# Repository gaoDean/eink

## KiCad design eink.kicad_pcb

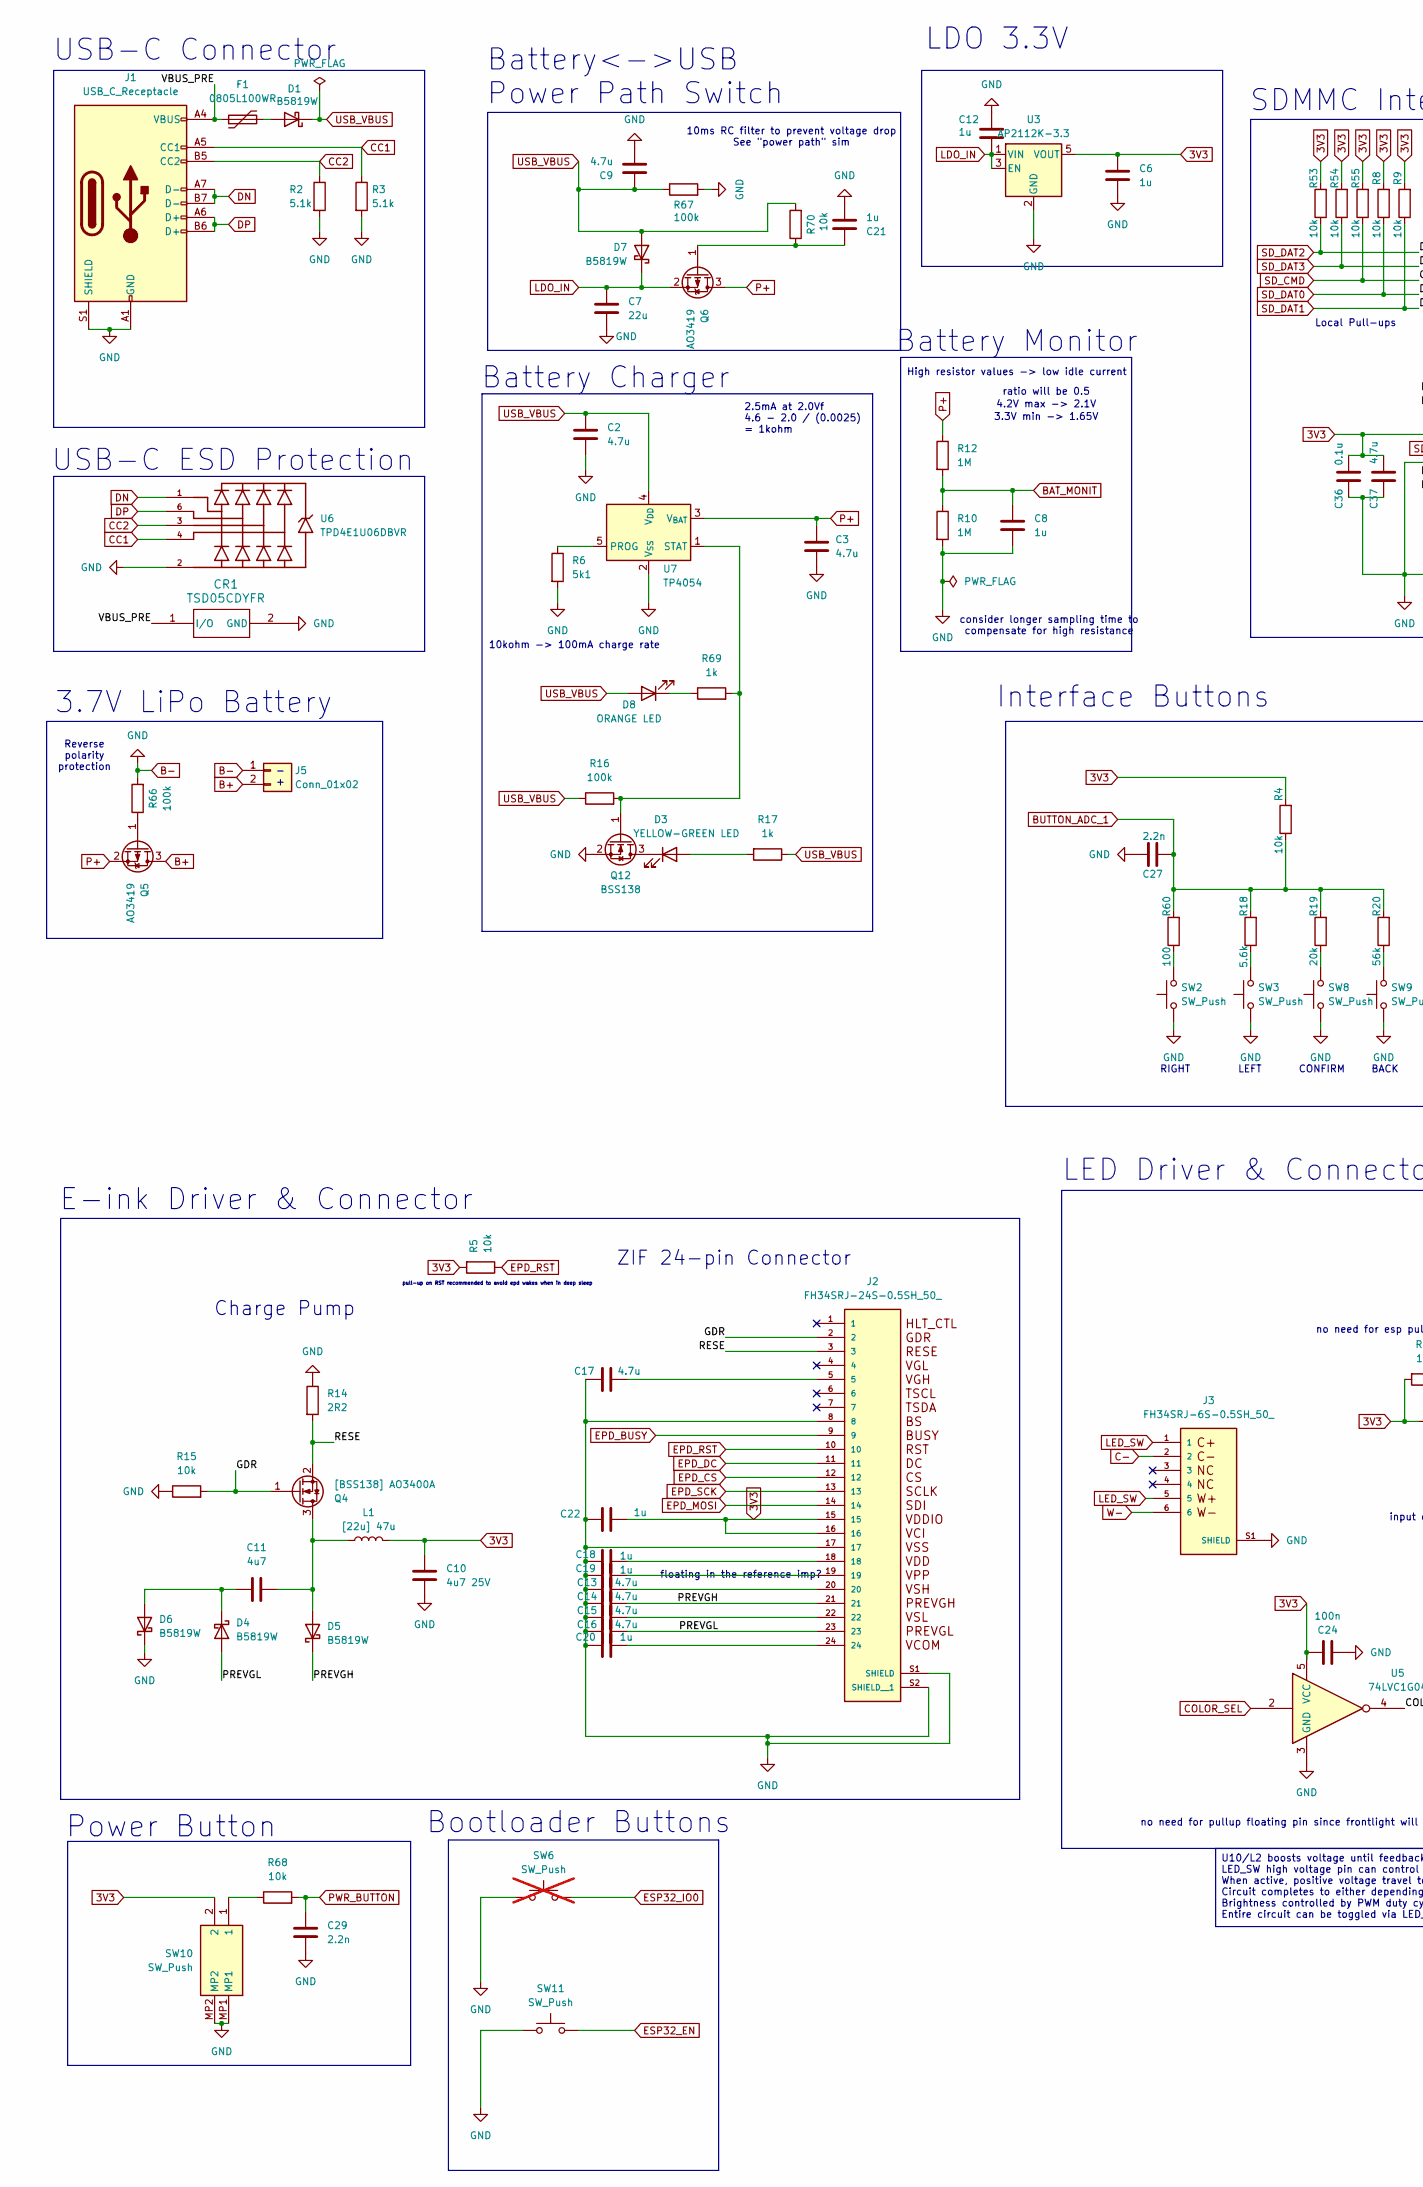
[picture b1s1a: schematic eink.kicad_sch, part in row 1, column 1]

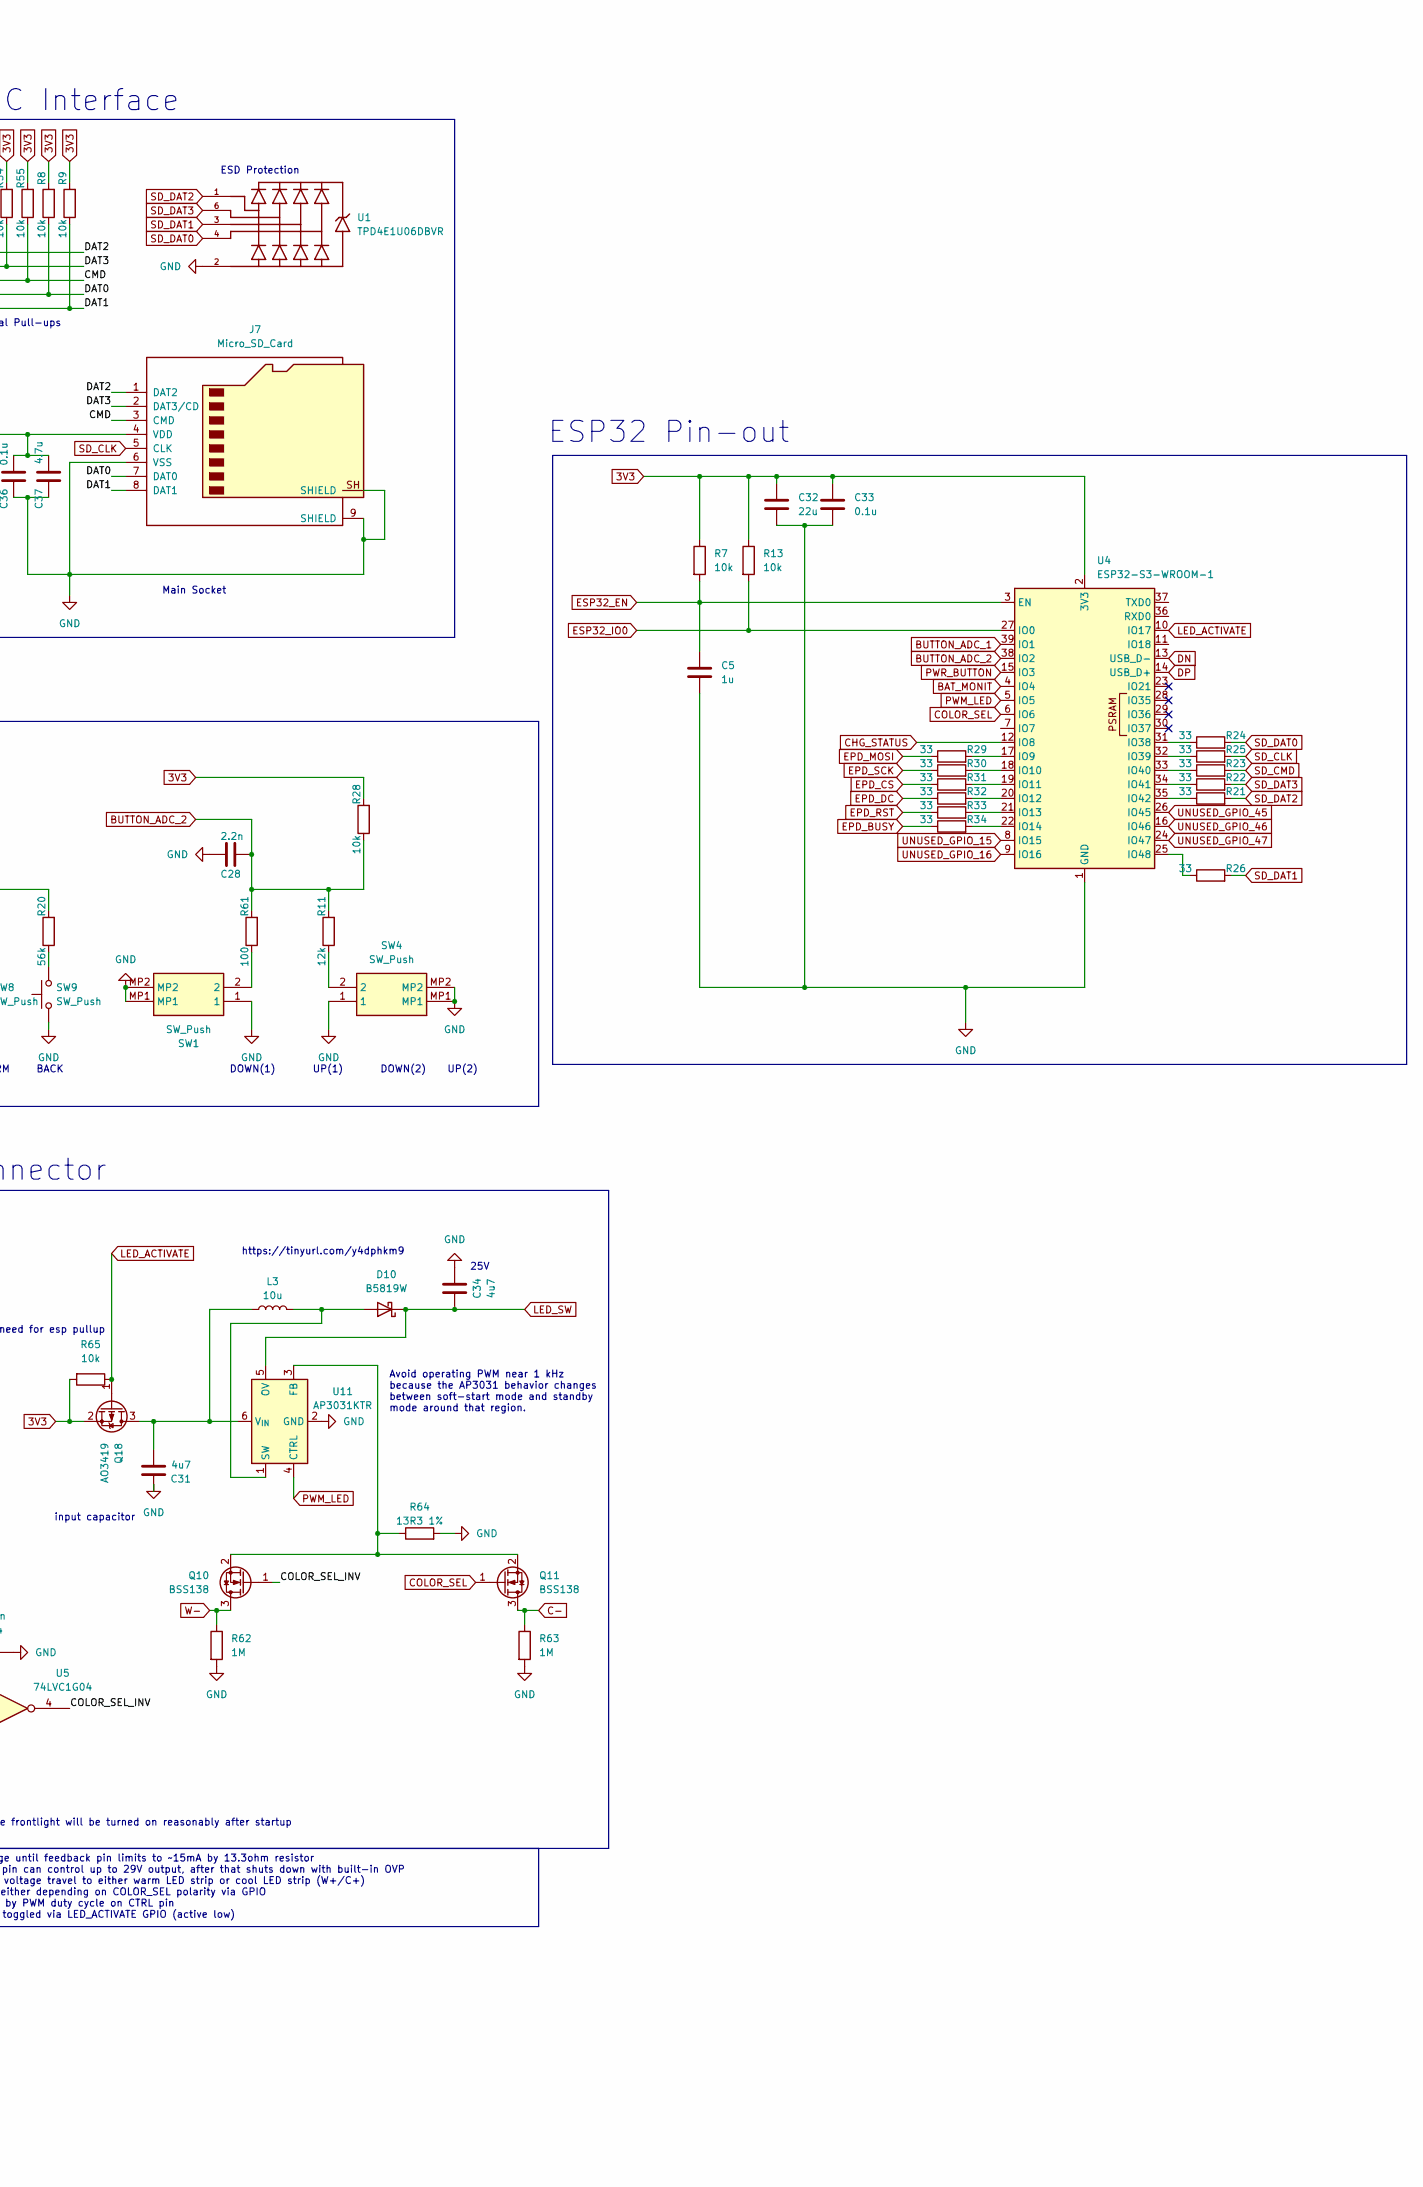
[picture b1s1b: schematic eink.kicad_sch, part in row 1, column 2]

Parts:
C2, C3, C9, C13, C14, C15, C16, C17, C37: 4.7u; C_0805_2012Metric_Pad1.18x1.45mm_HandSolder
C5, C6, C8, C12, C18, C19, C20, C21, C22: 1u; C_0805_2012Metric_Pad1.18x1.45mm_HandSolder
C7, C32: 22u; C_0805_2012Metric_Pad1.18x1.45mm_HandSolder
C10: 4u7 25V; C_0805_2012Metric_Pad1.18x1.45mm_HandSolder
C11, C31, C34: 4u7; C_0805_2012Metric_Pad1.18x1.45mm_HandSolder
C24: 100n; C_0805_2012Metric_Pad1.18x1.45mm_HandSolder
C27, C28, C29: 2.2n; C_0805_2012Metric_Pad1.18x1.45mm_HandSolder
C33, C36: 0.1u; C_0805_2012Metric_Pad1.18x1.45mm_HandSolder
CR1: TSD05CDYFR; D_SOD-323_HandSoldering
D1, D4, D5, D6, D7, D10: B5819W; D_SOD-123
D3: YELLOW-GREEN LED; LED_0805_2012Metric_Pad1.15x1.40mm_HandSolder
D8: ORANGE LED; LED_0805_2012Metric_Pad1.15x1.40mm_HandSolder
F1: 0805L100WR; Fuse_0805_2012Metric_Pad1.15x1.40mm_HandSolder
J1: USB_C_Receptacle; USB_C_Receptacle_TYPE-C-16P-CB1-6-073
J2: FH34SRJ-24S-0.5SH_50_; HRS_FH34SRJ-24S-0.5SH_50_
J3: FH34SRJ-6S-0.5SH_50_; HRS_FH34SRJ-6S-0.5SH_50_; DigiKey_Part_Number H125773CT-ND
J5: Conn_01x02; Battery pads
J7: Micro_SD_Card; microSD_HC_Hirose_DM3AT-SF-PEJM5
L1: [22u] 47u; IND_SRN3010C-100M
L3: 10u; IND_SRN3010C-100M
Q4: [BSS138] AO3400A; SOT-23
Q5, Q6, Q18: AO3419; SOT-23_Handsoldering
Q10, Q11, Q12: BSS138; SOT-23
R2, R3: 5.1k; R_0805_2012Metric_Pad1.20x1.40mm_HandSolder
R4, R5, R7, R8, R9, R13, R15, R28, R53, R54, R55, R65, R68, R70: 10k; R_0805_2012Metric_Pad1.20x1.40mm_HandSolder
R6: 5k1; R_0805_2012Metric_Pad1.20x1.40mm_HandSolder
R10, R12, R62, R63: 1M; R_0805_2012Metric_Pad1.20x1.40mm_HandSolder
R11: 12k; R_0805_2012Metric_Pad1.20x1.40mm_HandSolder
R14: 2R2; R_0805_2012Metric_Pad1.20x1.40mm_HandSolder
R16, R66, R67: 100k; R_0805_2012Metric_Pad1.20x1.40mm_HandSolder
R17, R69: 1k; R_0805_2012Metric_Pad1.20x1.40mm_HandSolder
R18: 5.6k; R_0805_2012Metric_Pad1.20x1.40mm_HandSolder
R19: 20k; R_0805_2012Metric_Pad1.20x1.40mm_HandSolder
R20: 56k; R_0805_2012Metric_Pad1.20x1.40mm_HandSolder
R21, R22, R23, R24, R25, R26, R29, R30, R31, R32, R33, R34: 33; R_0805_2012Metric_Pad1.20x1.40mm_HandSolder
R60, R61: 100; R_0805_2012Metric_Pad1.20x1.40mm_HandSolder
R64: 13R3 1%; R_0805_2012Metric_Pad1.20x1.40mm_HandSolder
SW1, SW4, SW10: SW_Push; SKSNLAE010; Mouser Part Number 688-SKSNLAE010
SW2, SW3, SW8, SW9: SW_Push; SKQGABE010_ALPS_Reverse
SW6: SW_Push; TestPoint_Bridge_Pitch2.54mm_Drill1.0mm; not fitted
SW11: SW_Push; TestPoint_Bridge_Pitch2.54mm_Drill1.0mm
U1, U6: TPD4E1U06DBVR; SOT-23-6_Handsoldering; PARTREV D; DigiKey_Part_Number 296-35965-1-ND
U3: AP2112K-3.3; SOT-23-5_HandSoldering
U4: ESP32-S3-WROOM-1
U5: 74LVC1G04; SOT-23-5_HandSoldering
U7: TP4054; SOT-23-5
U11: AP3031KTR; SOT-23-6_Handsoldering

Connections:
3V3: C6.1, C10.2, C22.2, C24.1, C32.1, C33.1, C36.2, C37.2, J2.15, J2.16, J7.4 (VDD), L1.2, Q18.2 (S), R4.2, R5.2, R7.1, R8.2, R9.2, R13.1, R28.2, R53.2, R54.2, R55.2, R65.2, SW10.2, U3.5 (VOUT), U4.2 (3V3), U5.5 (VCC)
/COLOR_SEL_INV: Q10.1 (G), U5.4
/GDR: J2.2, Q4.1 (G), R15.2
/PREVGH: C14.2, D5.1 (K), J2.21
/PREVGL: C16.2, D4.2 (A), J2.23
/RESE: J2.3, Q4.2 (S), R14.2
/VBUS_PRE: CR1.1 (I/O), F1.1, J1.A4 (VBUS), J1.A9 (VBUS), J1.B4 (VBUS), J1.B9 (VBUS)
B+: J5.2, Q5.3 (D)
B-: C2.2, C3.2, C5.2, C6.2, C7.2, C8.2, C9.2, C10.1, C12.2, C13.1, C14.1, C15.1, C16.1, C17.1, C18.1, C19.1, C20.1, C21.2, C22.1, C24.2, C27.1, C28.1, C29.2, C31.1, C32.2, C33.2, C34.1, C36.1, C37.1, CR1.2 (GND), D6.1 (K), J1.A1 (GND), J1.A12 (GND), J1.B1 (GND), J1.B12 (GND), J1.S1 (SHIELD), J2.8, J2.17, J2.S1 (SHIELD), J2.S2 (SHIELD__1), J3.S1 (SHIELD), J3.S2 (SHIELD), J5.1, J7.6 (VSS), J7.9 (SHIELD), J7.SH (SHIELD), Q12.2 (S), R2.2, R3.2, R6.2, R10.2, R14.1, R15.1, R62.2, R63.2, R64.2, R66.2, R67.2, SW1.1, SW1.MP1, SW1.MP2, SW2.1, SW3.1, SW4.1, SW4.MP1, SW4.MP2, SW6.1, SW8.1, SW9.1, SW10.MP1, SW10.MP2, SW11.1, U1.2, U3.2 (GND), U4.1 (GND), U4.40 (GND), U4.41 (GND), U5.3 (GND), U6.2, U7.2 (V_{SS}), U11.2 (GND)
BAT_MONIT: C8.1, R10.1, R12.2, U4.4 (IO4)
BUTTON_ADC_1: C27.2, R4.1, R18.2, R19.2, R20.2, R60.2, U4.39 (IO1)
BUTTON_ADC_2: C28.2, R11.2, R28.1, R61.2, U4.38 (IO2)
C-: J3.2, Q11.3 (D), R63.1
CC1: J1.A5 (CC1), R3.1, U6.4
CC2: J1.B5 (CC2), R2.1, U6.3
CHG_STATUS: U4.12 (IO8)
COLOR_SEL: Q11.1 (G), U4.6 (IO6), U5.2
DN: J1.A7 (D-), J1.B7 (D-), U4.13 (USB_D-), U6.1
DP: J1.A6 (D+), J1.B6 (D+), U4.14 (USB_D+), U6.6
EPD_BUSY: J2.9, R34.1
EPD_CS: J2.12, R31.1
EPD_DC: J2.11, R32.1
EPD_MOSI: J2.14, R29.1
EPD_RST: J2.10, R5.1, R33.1
EPD_SCK: J2.13, R30.1
ESP32_EN: C5.1, R7.2, SW11.2, U4.3 (EN)
ESP32_IO0: R13.2, SW6.2, U4.27 (IO0)
LDO_IN: C7.1, C12.1, D7.1 (K), Q6.2 (S), U3.1 (VIN), U3.3 (EN)
LED_ACTIVATE: Q18.1 (G), R65.1, U4.10 (IO17)
LED_SW: C34.2, D10.1 (K), J3.1, J3.5, U11.5 (OV)
unnamed: C13.2, J2.20
unnamed: C15.2, J2.22
unnamed: C17.2, J2.5
unnamed: C18.2, J2.18
unnamed: C19.2, J2.19
unnamed: C20.2, J2.24
unnamed: D1.2 (A), F1.2
unnamed: D3.2 (A), R17.2
unnamed: D3.1 (K), Q12.3 (D)
unnamed: C11.1, D4.1 (K), D6.2 (A)
unnamed: C11.2, D5.2 (A), L1.1, Q4.3 (D)
unnamed: D8.1 (K), R69.1
unnamed: D10.2 (A), L3.2, U11.1 (SW)
unnamed: Q5.1 (G), R66.1
unnamed: C21.1, Q6.1 (G), R70.1
unnamed: Q10.2 (S), Q11.2 (S), R64.1, U11.3 (FB)
unnamed: Q12.1 (G), R16.2, R69.2, U7.1 (STAT)
unnamed: C31.2, L3.1, Q18.3 (D), U11.6 (V_{IN})
unnamed: R11.1, SW4.2
unnamed: R18.1, SW3.2
unnamed: R19.1, SW8.2
unnamed: R20.1, SW9.2
unnamed: R60.1, SW2.2
unnamed: R61.1, SW1.2
unnamed: R68.1, SW10.1
unnamed: R29.2, U4.17 (IO9)
unnamed: R30.2, U4.18 (IO10)
unnamed: R31.2, U4.19 (IO11)
unnamed: R32.2, U4.20 (IO12)
unnamed: R33.2, U4.21 (IO13)
unnamed: R34.2, U4.22 (IO14)
unnamed: R24.1, U4.31 (IO38)
unnamed: R25.1, U4.32 (IO39)
unnamed: R23.1, U4.33 (IO40)
unnamed: R22.1, U4.34 (IO41)
unnamed: R21.1, U4.35 (IO42)
unnamed: R26.1, U4.25 (IO48)
unnamed: R6.1, U7.5 (PROG)
P+: C3.1, Q5.2 (S), Q6.3 (D), R12.1, U7.3 (V_{BAT})
PWM_LED: U4.5 (IO5), U11.4 (CTRL)
PWR_BUTTON: C29.1, R68.2, U4.15 (IO3)
SD_CLK: J7.5 (CLK), R25.2
SD_CMD: J7.3 (CMD), R23.2, R55.1
SD_DAT0: J7.7 (DAT0), R8.1, R24.2, U1.4
SD_DAT1: J7.8 (DAT1), R9.1, R26.2, U1.3
SD_DAT2: J7.1 (DAT2), R21.2, R53.1, U1.1
SD_DAT3: J7.2 (DAT3/CD), R22.2, R54.1, U1.6
UNUSED_GPIO_15: U4.8 (IO15)
UNUSED_GPIO_16: U4.9 (IO16)
UNUSED_GPIO_45: U4.26 (IO45)
UNUSED_GPIO_46: U4.16 (IO46)
UNUSED_GPIO_47: U4.24 (IO47)
USB_VBUS: C2.1, C9.1, D1.1 (K), D7.2 (A), D8.2 (A), R16.1, R17.1, R67.1, R70.2, U7.4 (V_{DD})
W-: J3.6, Q10.3 (D), R62.1

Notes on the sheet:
ratio will be 0.5
SDMMC Interface
2.5mA at 2.0Vf 4.6 - 2.0 / (0.0025) = 1kohm
Battery<->USB Power Path Switch
RIGHT LEFT CONFIRM BACK
no need for pullup floating pin since frontlight will be turned on reasonably after startup
3.7V LiPo Battery
input capacitor
Charge Pump
LED Driver & Connector
Interface Buttons
Avoid operating PWM near 1 kHz because the AP3031 behavior changes between soft-start mode and standby mode around that region.
3.3V min -> 1.65V
- +
25V
pull-up on RST recommended to avoid epd wakes when in deep sleep
E-ink Driver & Connector
ESD Protection
Battery Charger
consider longer sampling time to compensate for high resistance
10ms RC filter to prevent voltage drop See "power path" sim
ESP32 Pin-out
Reverse polarity protection
4.2V max -> 2.1V
ZIF 24-pin Connector
Local Pull-ups
DOWN(1) UP(1) DOWN(2) UP(2)
https://tinyurl.com/y4dphkm9
LDO 3.3V
Power Button
High resistor values -> low idle current
Battery Monitor
USB-C ESD Protection
USB-C Connector
Bootloader Buttons
10kohm -> 100mA charge rate
Main Socket
floating in the reference imp?
no need for esp pullup
U10/L2 boosts voltage until feedback pin limits to ~15mA by 13.3ohm resistor LED_SW high voltage pin can control up to 29V output, after that shuts down with built-in OVP When active, positive voltage travel to either warm LED strip or cool LED strip (W+/C+) Circuit completes to either depending on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

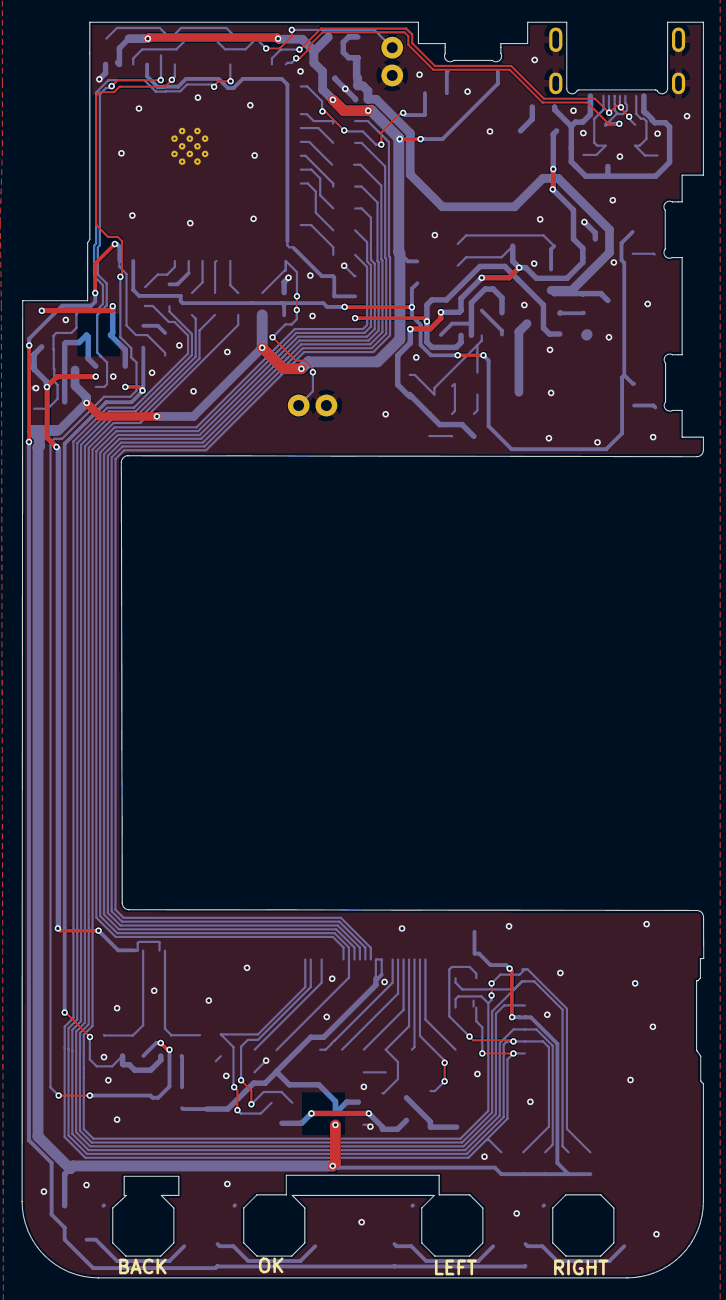
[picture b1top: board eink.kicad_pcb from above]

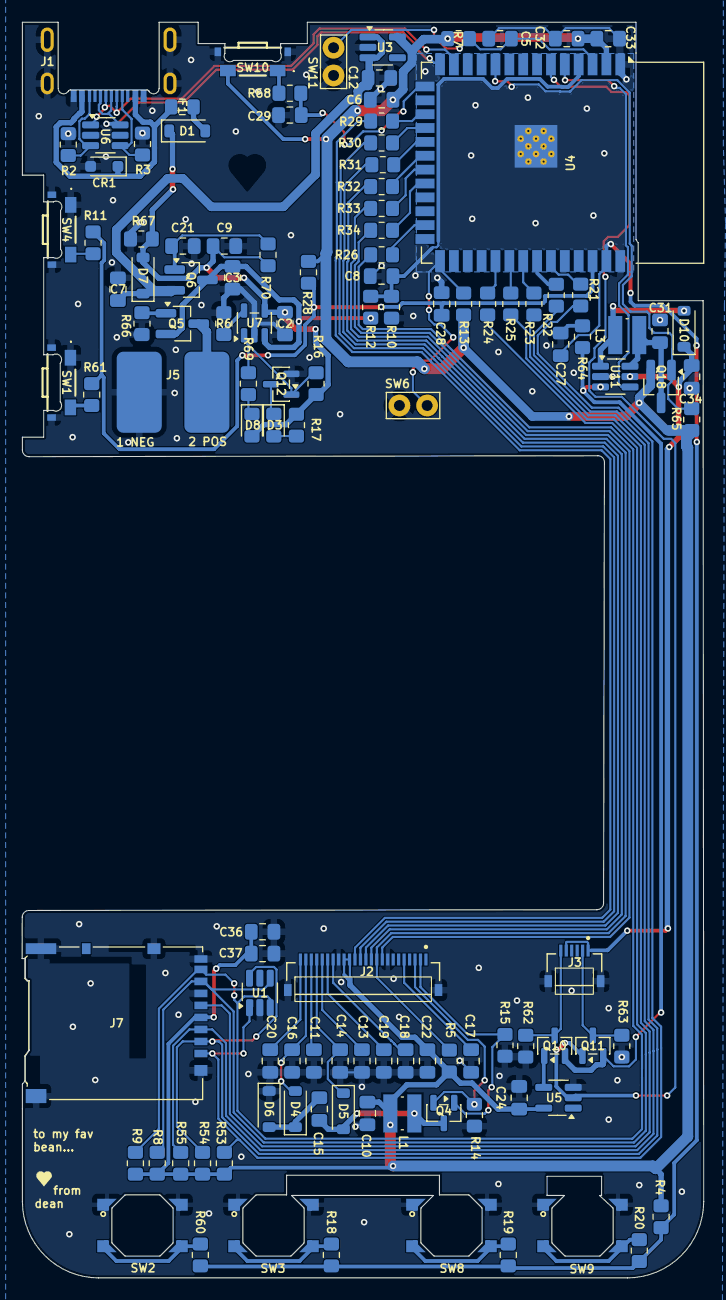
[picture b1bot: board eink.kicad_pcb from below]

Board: 2 copper layers, 62.4 x 115.0 mm, 116 parts (116 on the bottom side), 78 nets.

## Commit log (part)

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2026-06-13 first draft for 1.0
2026-06-18 update silkscreen
2026-06-23 revised layout for emi/emc
2026-06-24 added fuse changed mbr to b5819w for current rating increase changed r38 to reduce leakage spiffied up silkscreen
2026-06-24 updated parts sheet
